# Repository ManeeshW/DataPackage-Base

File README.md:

# ONR Data Package

## Dependencies (C++)
### Base
```sh
sudo apt install python3-pip
sudo apt install cmake libgtkmm-3.0-dev # if Linux base
sudo apt install libserialport-dev

brew install gtkmm3 pygobject3 # if Mac base
```

##### Add your user to the dialout group:
```sh
sudo usermod -aG dialout $(whoami)
groups
```
##### Log out and log back in (or reboot) for the changes to take effect.

### Rover
```sh
sudo apt install cmake
sudo apt install build-essential
sudo apt install doxygen

# SBP library
cd libraries/libsbp/c
mkdir build
cd build
cmake ../
make
sudo make install

git clone --branch v2.7.4 https://github.com/swift-nav/libsbp.git
git submodule update --init
cd libsbp/
git submodule update --init
cd c/
mkdir build
cd build/
cmake ../
make
sudo make install
cd ..
cd python/
pip install .
```
#### new update
```sh
nm-connection-editor
git clone --branch v2.7.4 https://github.com/swift-nav/libsbp.git
git submodule update --init
cd libsbp/
git submodule update --init
cd c/
mkdir build
cd build/
cmake ../
make
sudo make install
cd ..
cd python/
pip install .
```

1. Install `libserialport`: [https://github.com/fdcl-gwu/libserialport](https://github.com/fdcl-gwu/libserialport)

## Dependencies (Python)
### Mac
```sh
conda create --name python39 python==3.9
conda activate python39

brew install gtk+3 pygobject3

pip3 install pgi
pip3 install pycairo
pip3 install numpy
pip3 install matplotlib
pip3 install pandas

pip3 install sbp

conda install protobuf

```

### Rover
```sh
sudo pip3 install adafruit-circuitpython-bno055
sudo pip3 install Adafruit-Blinka
pip3 install sbp

sudo apt install -y protobuf-compiler
```

## Compiling proto message
```sh
protoc data.proto --python_out=./proto
```

## Troubleshooting
* ModuleNotFoundError: No module named 'gi'
```sh
export PYTHONPATH=/usr/local/lib/python3.9/site-packages/ 
```

## Alias
```bash
alias gtbp="cd onr-data-package/scripts/"
alias rbp="python3 base.py"
```

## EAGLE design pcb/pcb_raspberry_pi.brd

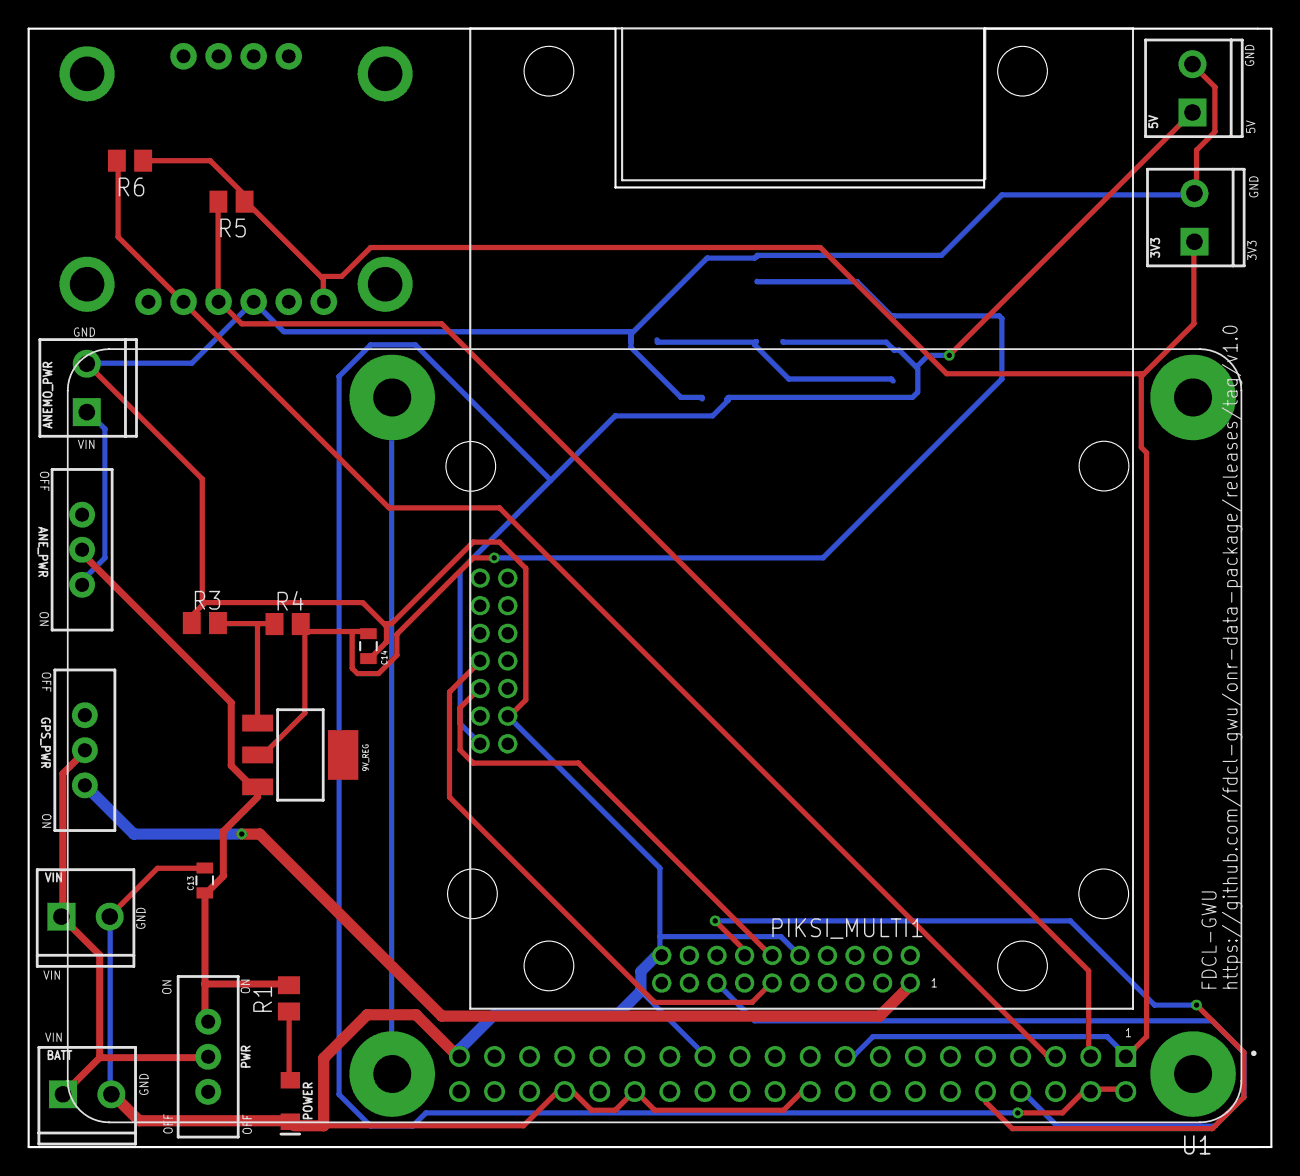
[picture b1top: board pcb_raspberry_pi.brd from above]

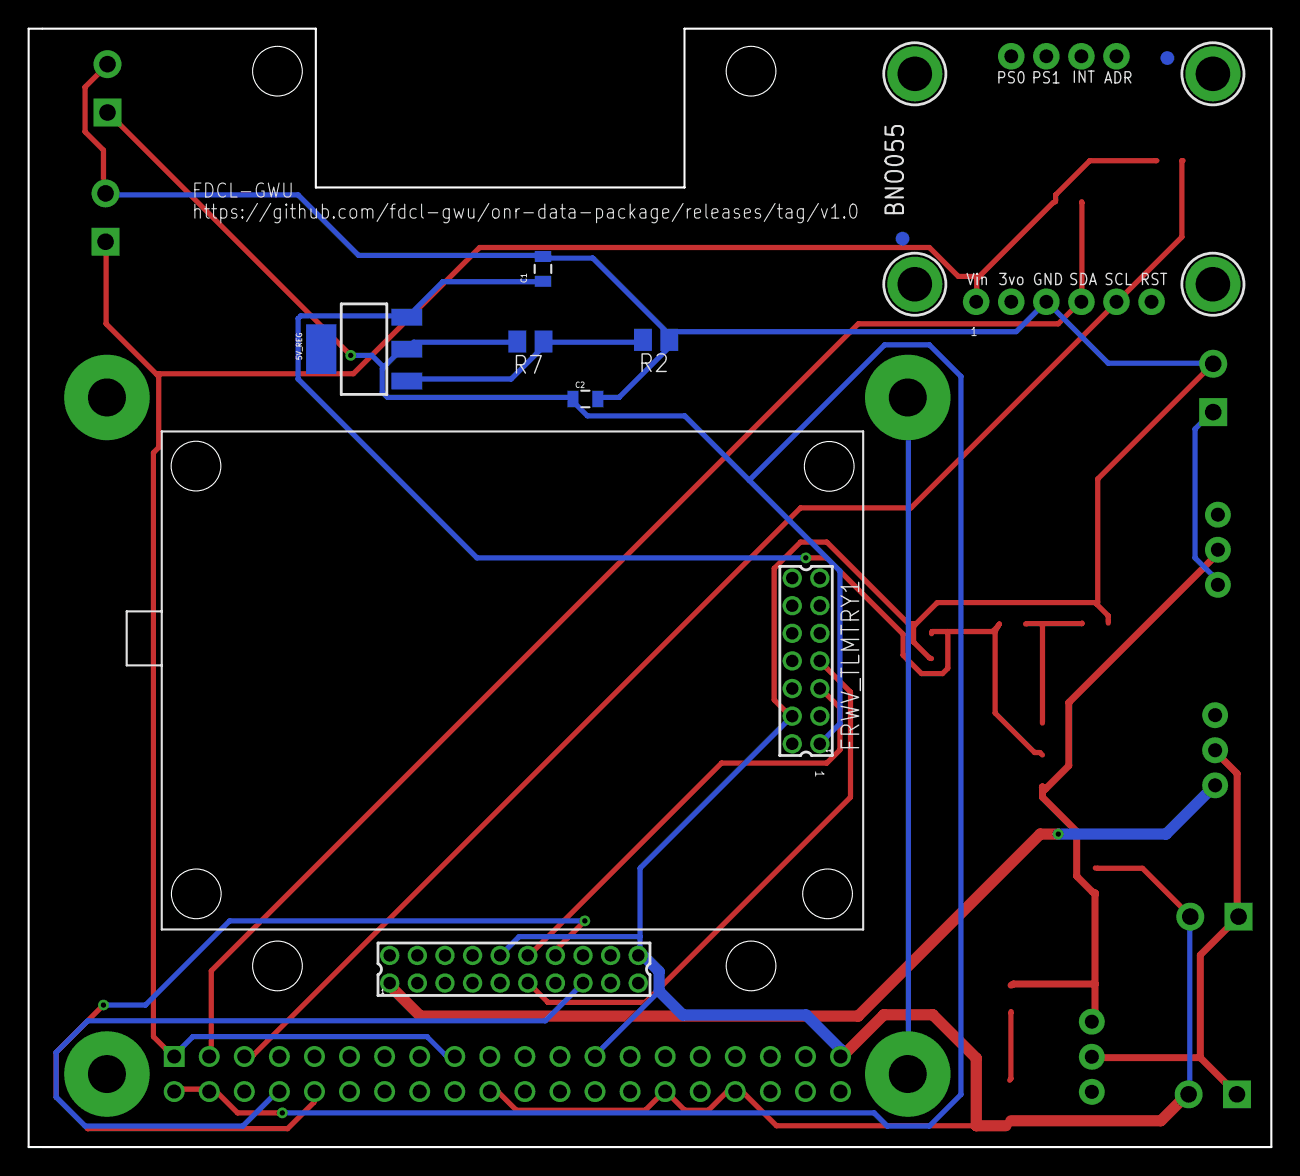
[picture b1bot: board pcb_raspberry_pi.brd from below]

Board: 2 copper layers, 90.0 x 81.0 mm, 33 parts (15 on the bottom side), 18 nets.

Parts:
3V3, 5V: SCREWTERMINAL-3.5MM-2
5V_REG, 9V_REG: V_REG_317SMD; SOT223
ANEMO_PWR: SCREWTERMINAL-3.5MM-2
ANE_PWR: SWITCH_SPDT_PTH_11.6X4.0MM
BATT: SCREWTERMINAL-3.5MM-2
C1, C13: 0.1UF; 0805
C2, C14: 1UF; 0805
FID3, FID4: FIDUCIAL""; FIDUCIAL_1MM
FRWV_TLMTRY1: 87758-1416
GPS_PWR: SWITCH_SPDT_PTH_11.6X4.0MM
JP3: 1X06_ROUND_76
JP4: 1X04_ROUND_76
PIKSI_MULTI1: 332-20
POWER: GREEN; LED-1206
PWR: SWITCH_SPDT_PTH_11.6X4.0MM
R1: 68.1k; M2012
R2: 750; M2012
R3: 1.5k; M2012
R4, R7: 240; M2012
R5: 3.3k; M2012
R6: 2.2k; M2012
U1: RASPBERRY_PI_3_MODEL_B+; MODULE_RASPBERRY_PI_3_MODEL_B+
U$1, U$2, U$3, U$4: MOUNTINGHOLE2.5_THICK; MOUNTINGHOLE_2.5_PLATED_THICK
VIN: SCREWTERMINAL-3.5MM-2

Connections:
+5V: 5V.1, 5V_REG.2, C2.1, FRWV_TLMTRY1.1, R7.2, U1.2, U1.4
+9V: 5V_REG.3, 9V_REG.2, C1.1, C14.1, R4.2
+12V: 9V_REG.3, ANE_PWR.2, C13.1, PWR.3, R1.2
ANE_ON: ANEMO_PWR.1, ANE_PWR.3
GND: 3V3.2, 5V.2, ANEMO_PWR.2, BATT.2, C1.2, C2.2, C13.2, C14.2, FRWV_TLMTRY1.4, JP3.3, PIKSI_MULTI1.10, PIKSI_MULTI1.20, POWER.C, R2.1, R3.1, U1.20, U1.25, U1.30, U1.34, U1.39, VIN.2
GPS_ON: GPS_PWR.3, PIKSI_MULTI1.1
GPS_RX0: FRWV_TLMTRY1.5, PIKSI_MULTI1.12
GPS_RX1: PIKSI_MULTI1.15, U1.8
GPS_TX0: FRWV_TLMTRY1.7, PIKSI_MULTI1.11
GPS_TX1: PIKSI_MULTI1.14, U1.10
IMU_3V3: 3V3.1, JP3.1, R5.1, R6.1, U1.1, U1.17
IMU_SCL: JP3.5, R6.2, U1.5
IMU_SDA: JP3.4, R5.2, U1.3
unnamed: 9V_REG.1, R3.2, R4.1
unnamed: POWER.A, R1.1
unnamed: 5V_REG.1, R2.2, R7.1
S$1: U1.S2, U1.S3
VIN: BATT.1, GPS_PWR.2, PWR.2, VIN.1

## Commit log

2024-12-20 Base
2024-12-21 dialout

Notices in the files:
parts and their libraries:
SparkFun-Connectors: Licensing: Creative Commons ShareAlike 4.0 International - https://creativecommons.org/licenses/by-sa/4.0
microbuilder: This work is placed in the public domain, and may be freely used for commercial and non-commercial work with the following conditions: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
